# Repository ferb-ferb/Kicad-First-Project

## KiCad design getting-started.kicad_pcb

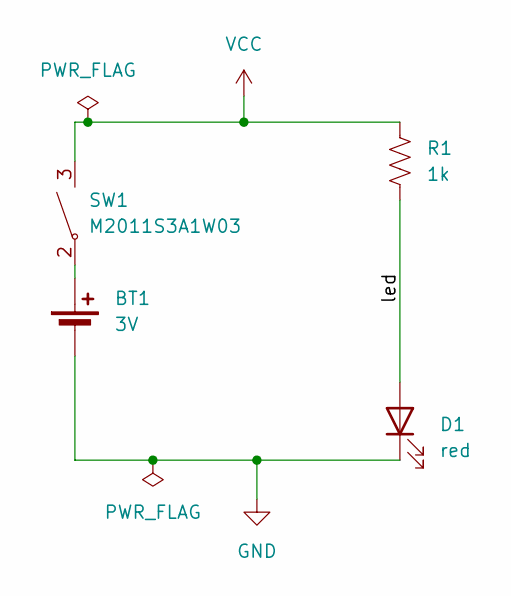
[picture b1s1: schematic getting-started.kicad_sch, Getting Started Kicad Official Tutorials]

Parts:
BT1: 3V; BatteryHolder_Keystone_1058_1x2032
D1: red; LED_D5.0mm
R1: 1k; R_Axial_DIN0309_L9.0mm_D3.2mm_P12.70mm_Horizontal
SW1: M2011S3A1W03

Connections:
/led: D1.2 (A), R1.2
GND: BT1.2 (-), D1.1 (K)
unnamed: BT1.1 (+), SW1.2 (A)
VCC: R1.1, SW1.3 (B)

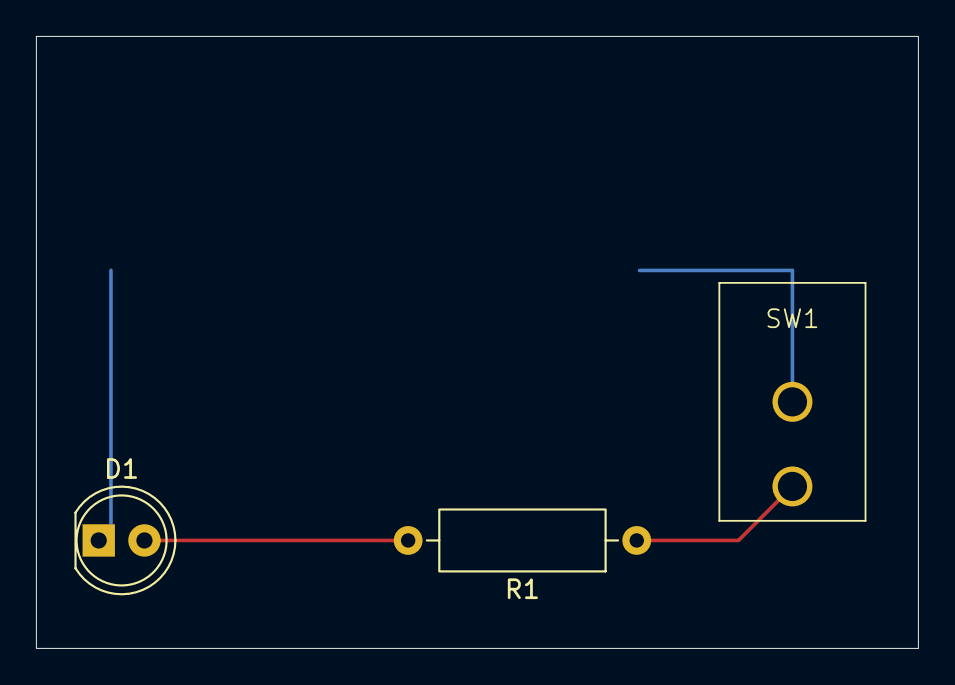
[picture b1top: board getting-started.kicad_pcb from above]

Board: 2 copper layers, 49.0 x 34.0 mm, 4 parts (1 on the bottom side), 4 nets.

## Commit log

2025-08-13 Initial Commit - Repo Setup
2025-08-13 Adding Project Files
2025-08-13 cleaning up
2025-08-13 Complete repository refresh with updated .gitignore
2025-08-13 Updated BOM
2025-08-13 fixing untitled custom footprint
2025-08-13 propogating changes through sch and bom
2025-08-13 propogating changes through pcb
